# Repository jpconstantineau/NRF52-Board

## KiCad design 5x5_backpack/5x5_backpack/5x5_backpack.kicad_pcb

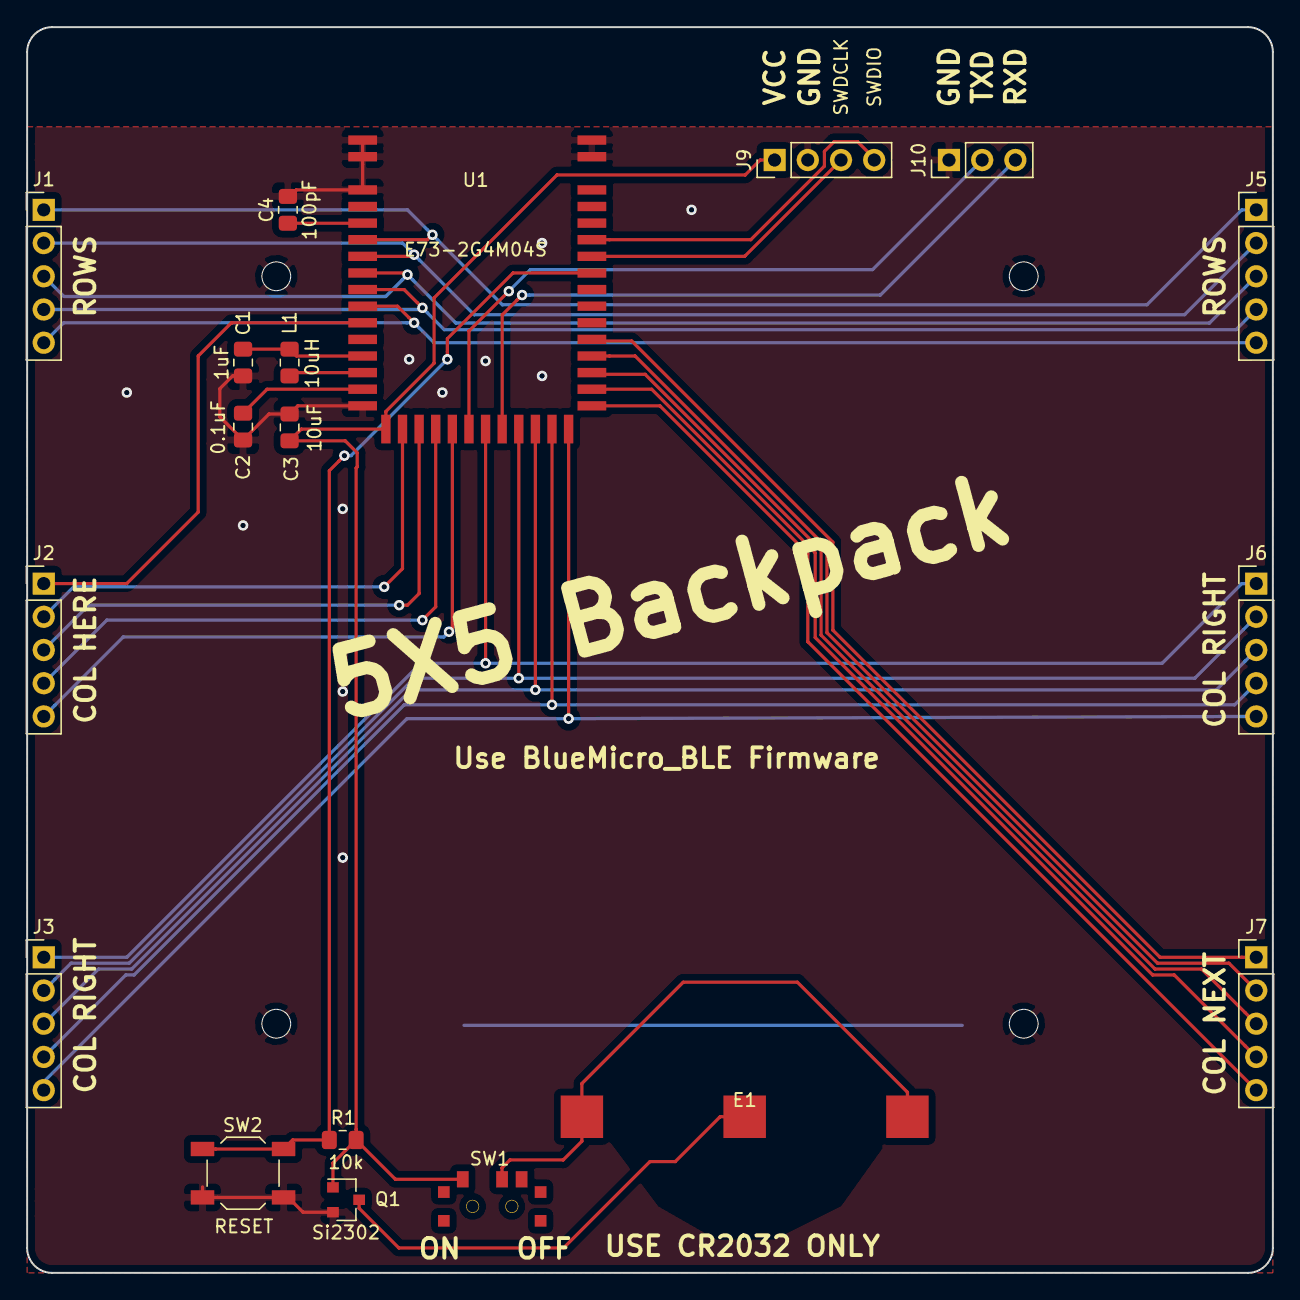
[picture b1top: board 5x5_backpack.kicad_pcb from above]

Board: 2 copper layers, 95.2 x 95.2 mm, 23 parts (0 on the bottom side), 33 nets.

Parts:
C1: 1uF; C_0805_2012Metric_Pad1.15x1.40mm_HandSolder
C2: 0.1uF; C_0805_2012Metric_Pad1.15x1.40mm_HandSolder
C3: 10uF; C_0805_2012Metric_Pad1.15x1.40mm_HandSolder
C4: 100pF; C_0805_2012Metric_Pad1.15x1.40mm_HandSolder
E1: Battery; C70373_CR2032
J1, J2, J3, J5, J6, J7: Conn_01x04; PinHeader_1x05_P2.54mm_Vertical
J9: Conn_01x04; PinHeader_1x04_P2.54mm_Vertical
J10: Conn_01x03; PinHeader_1x03_P2.54mm_Vertical
J11, J12, J13, J14: Conn_01x01; MountingHole_2.2mm_M2_ISO7380
L1: 10uH; C_0805_2012Metric_Pad1.15x1.40mm_HandSolder
Q1: Si2302; SOT-23
R1: 10k; C_0805_2012Metric_Pad1.15x1.40mm_HandSolder
SW1: SW_SPDT; SPDT_C128955
SW2: RESET; SW_TACT_ALPS_SKQGABE010
U1: E73-2G4M04S

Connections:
COL1: J2.1, U1.10
COL2: J2.2, U1.17
COL3: J2.3, U1.18
COL4: J2.4, U1.19
COL5: J2.5, U1.20
COL6: J3.1, J6.1, U1.22
COL7: J3.2, J6.2, U1.24
COL8: J3.3, J6.3, U1.25
COL9: J3.4, J6.4, U1.26
COL10: J3.5, J6.5, U1.27
COL11: J7.1, U1.32
COL12: J7.2, U1.31
COL13: J7.3, U1.30
COL14: J7.4, U1.29
COL15: J7.5, U1.28
GND: C1.2, C2.2, C3.2, C4.2, J9.2, J10.1, J11.1, J12.1, J13.1, J14.1, Q1.2, SW2.1, U1.0, U1.1, U1.2, U1.15, U1.42, U1.43
unnamed: C1.1, L1.1, U1.12
unnamed: C2.1, U1.14
unnamed: C4.1, U1.4
unnamed: E1.1, SW1.2
unnamed: E1.2, Q1.3
unnamed: L1.2, U1.13
RESET: R1.2, SW2.2, U1.36
ROW1: J1.1, J5.1, U1.5
ROW2: J1.2, J5.2, U1.6
ROW3: J1.3, J5.3, U1.7
ROW4: J1.4, J5.4, U1.8
ROW5: J1.5, J5.5, U1.9
RXD: J10.3, U1.23
SWDCLK: J9.3, U1.37
SWDIO: J9.4, U1.38
TXD: J10.2, U1.21
VCC: C3.1, J9.1, Q1.1, R1.1, SW1.1, U1.16

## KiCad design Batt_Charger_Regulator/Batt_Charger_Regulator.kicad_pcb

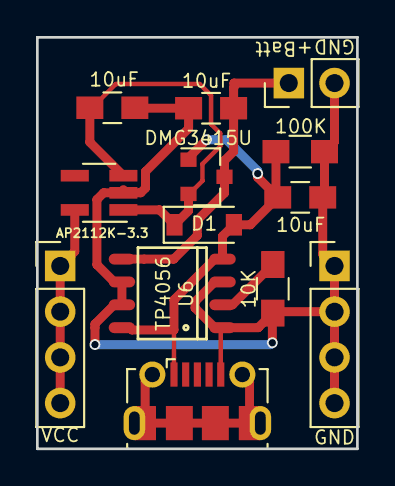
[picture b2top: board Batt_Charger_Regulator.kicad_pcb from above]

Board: 2 copper layers, 17.8 x 22.9 mm, 13 parts (0 on the bottom side), 6 nets.

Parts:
C5, C7, C8: 10uF; C_0805_HandSoldering
D1: MBR120; D_SOD-123
J1: USB_OTG; USB_Micro-B_Molex-105017-0001
J2, J4: Conn_01x04; Pin_Header_Straight_1x04_Pitch2.54mm
J3: Conn_01x02; Pin_Header_Straight_1x02_Pitch2.54mm
Q1: DMG3415U; SOT-23
R2: 100K; R_0805_HandSoldering
R3: 10K; R_0805_HandSoldering
U3: AP2112K-3.3; SOT-23-5_HandSoldering
U6: TP4056; SO-8

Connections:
/VBatt: C7.1, J3.1, Q1.3, U6.5
/VBus: C8.1, D1.2, J1.1, Q1.1, R2.1, U6.4, U6.8
GND: C5.2, C7.2, C8.2, J1.5, J2.1, J2.2, J2.3, J2.4, J3.2, R2.2, R3.2, U3.2, U6.1, U6.3, U6.6, U6.7
unnamed: C5.1, D1.1, Q1.2, U3.1, U3.3
unnamed: R3.1, U6.2
VCC: J4.1, J4.2, J4.3, J4.4, U3.5

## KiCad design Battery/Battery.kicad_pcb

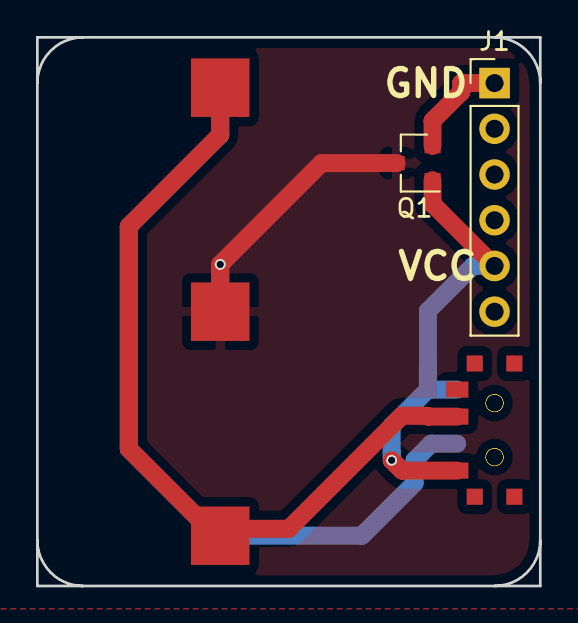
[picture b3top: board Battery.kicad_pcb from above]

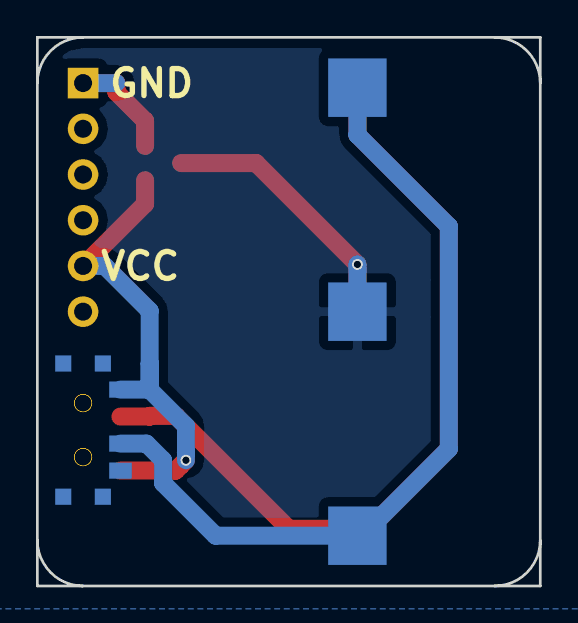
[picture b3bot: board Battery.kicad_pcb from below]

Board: 2 copper layers, 27.9 x 30.5 mm, 6 parts (2 on the bottom side), 5 nets.

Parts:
BT1, BT2: Battery_Cell; C70373_CR2032
J1: Conn_01x06; Pin_Header_Straight_1x06_Pitch2.54mm
Q1: BSS138; SOT-23
SW1, SW2: SW_SPDT; SPDT_C128955

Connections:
GND: BT1.2, BT2.2, Q1.3
unnamed: BT1.1, SW1.2
unnamed: BT2.1, SW2.2
unnamed: J1.1, Q1.2
VCC: J1.5, Q1.1, SW1.1, SW2.1

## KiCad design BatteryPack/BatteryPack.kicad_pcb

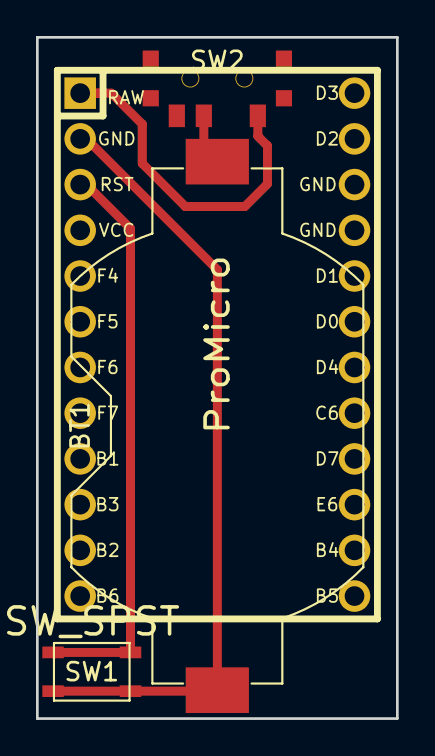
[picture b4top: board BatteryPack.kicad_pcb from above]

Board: 2 copper layers, 20.0 x 37.8 mm, 4 parts (0 on the bottom side), 4 nets.

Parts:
BT1: Battery_Cell; Keystone_1058_1x2032-CoinCell
SW1: SW_SPST; SW_TACT_TS-1145A_C318904
SW2: SW_SPDT; SPDT_C128955
U1: ProMicro; Pro_Micro

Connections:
GND: BT1.2, SW1.2, U1.2
unnamed: BT1.1, SW2.2
unnamed: SW1.1, U1.3
unnamed: SW2.1, U1.1

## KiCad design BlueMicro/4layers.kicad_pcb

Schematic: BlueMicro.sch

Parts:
C1: 1uF; C_0603_1608Metric
C2, C10: 0.1uF; C_0603_1608Metric
C3, C11, C12, C13: 10uF; C_0603_1608Metric
C4: 100pF; C_0603_1608Metric
C5, C8: 22pF; C_0603_1608Metric
C6, C7, C9: 100nF; C_0603_1608Metric
C14: 1nF; C_0603_1608Metric
D1: BLUE; LED_0603_1608Metric
D2, D5, D6, D10: RED; LED_0603_1608Metric
D3, D4, D7: 1N4148W; D_SOD-123
D8: B5819W; D_SOD-123
D9: GREEN; LED_0603_1608Metric
J9: Conn_01x04; PinHeader_1x04_P2.54mm_Vertical
J10: Conn_01x02; PinHeader_1x02_P2.54mm_Vertical
J17: USB_B_Micro; USB_Micro-B_Molex-105017-0001
L1: 10uH; L_0603_1608Metric
Q1: Si2301CDS; SOT-23
R1, R7, R9: 10k; R_0603_1608Metric
R2, R3, R4, R5, R6, R10: 1k; R_0603_1608Metric
R8: 100k; R_0603_1608Metric
R11: 806k; R_0603_1608Metric
R12: 2M; R_0603_1608Metric
TP1, TP2, TP3, TP4, TP5, TP6, TP7: TestPoint_Probe; TestPoint_Pad_1.0x1.0mm
U1: E73-2G4M04S
U2: CH340G; SOP-16_4.4x10.4mm_P1.27mm
U3: TP4056; SSOP-8_3.95x5.21x3.27mm_P1.27mm
U4: AP2112K-3.3; SOT-23-5
U5: ProMicro; Pro_Micro
Y1: 12MHz; Crystal_SMD_3225-4Pin_3.2x2.5mm

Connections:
B1: U1.27, U5.9
B2: U1.28, U5.11
B3: U1.29, U5.10
B4: U1.30, U5.23
B5: U1.31, U5.24
B6: U1.26, U5.12
BLUELED: D1.2, U1.34
C6: U1.8, U5.20
D0: U1.6, U5.18
D1: U1.5, U5.17
D2: U1.22, U5.14
D3: U1.33, U5.13
D4: U1.7, U5.19
D7: U1.9, U5.21
DFU: TP4.1, U1.35
DTR: C10.2, U2.13
E6: U1.10, U5.22
F4: U1.20, U5.5
F5: U1.19, U5.6
F6: U1.18, U5.7
F7: U1.17, U5.8
FACTORYRESET: TP3.1, U1.39
GND: C1.2, C2.2, C3.2, C4.2, C5.2, C6.2, C7.2, C8.2, C9.2, C11.2, C12.2, C13.2, C14.2, J9.2, J10.2, J17.5, R2.2, R3.2, R7.1, R8.1, R12.2, U1.0, U1.1, U1.2, U1.15, U1.42, U1.43, U2.1, U3.1, U3.3, U4.2, U5.2, U5.15, U5.16, Y1.2, Y1.4; also elsewhere on the board
NFC1: TP5.1, U1.24
NFC2: TP6.1, U1.25
unnamed: C1.1, L1.1, U1.12
unnamed: C2.1, U1.14
unnamed: C4.1, U1.4
unnamed: C5.1, U2.7, Y1.1
unnamed: C7.1, U2.4
unnamed: C8.1, U2.8, Y1.3
unnamed: C9.1, D4.1, R5.2, R6.1, U2.16
unnamed: C12.1, D8.1, Q1.2 (S), U4.1, U4.3
unnamed: C14.1, R11.2, R12.1, U1.11
unnamed: D1.1, R2.1
unnamed: D2.1, R3.1
unnamed: D3.1, D4.2
unnamed: D5.2, R5.1
unnamed: D6.2, R6.2
unnamed: D9.1, U3.6
unnamed: D9.2, R9.2
unnamed: D10.1, U3.7
unnamed: D10.2, R10.2
unnamed: J17.2, U2.6
unnamed: J17.3, U2.5
unnamed: L1.2, U1.13
unnamed: R4.1, U2.2
unnamed: R7.2, U3.2
PWM: TP2.1, U1.40
REDLED: D2.2, U1.32
RESET: C10.1, D7.2, R1.2, U1.36, U5.3; also elsewhere on the board
RXD: D6.1, R4.2, U1.23
SWDCLK: J9.3, U1.37
SWDIO: J9.4, U1.38
TXD: D5.1, U1.21, U2.3
VBATT: C13.1, J10.1, Q1.3 (D), R11.1, U3.5
VBUS: C6.1, C11.1, D3.2, D8.2, J17.1, Q1.1 (G), R8.2, R9.1, R10.1, U3.4, U3.8
VCC: C3.1, D7.1, J9.1, R1.1, U1.16, U4.5, U5.4
WS2812B: TP1.1, U1.41

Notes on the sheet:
1 - diodes provide close enough to 3.3v for the serial chip. 2 - To ensure low battery consumption when USB is not connected, Only GND is shared.

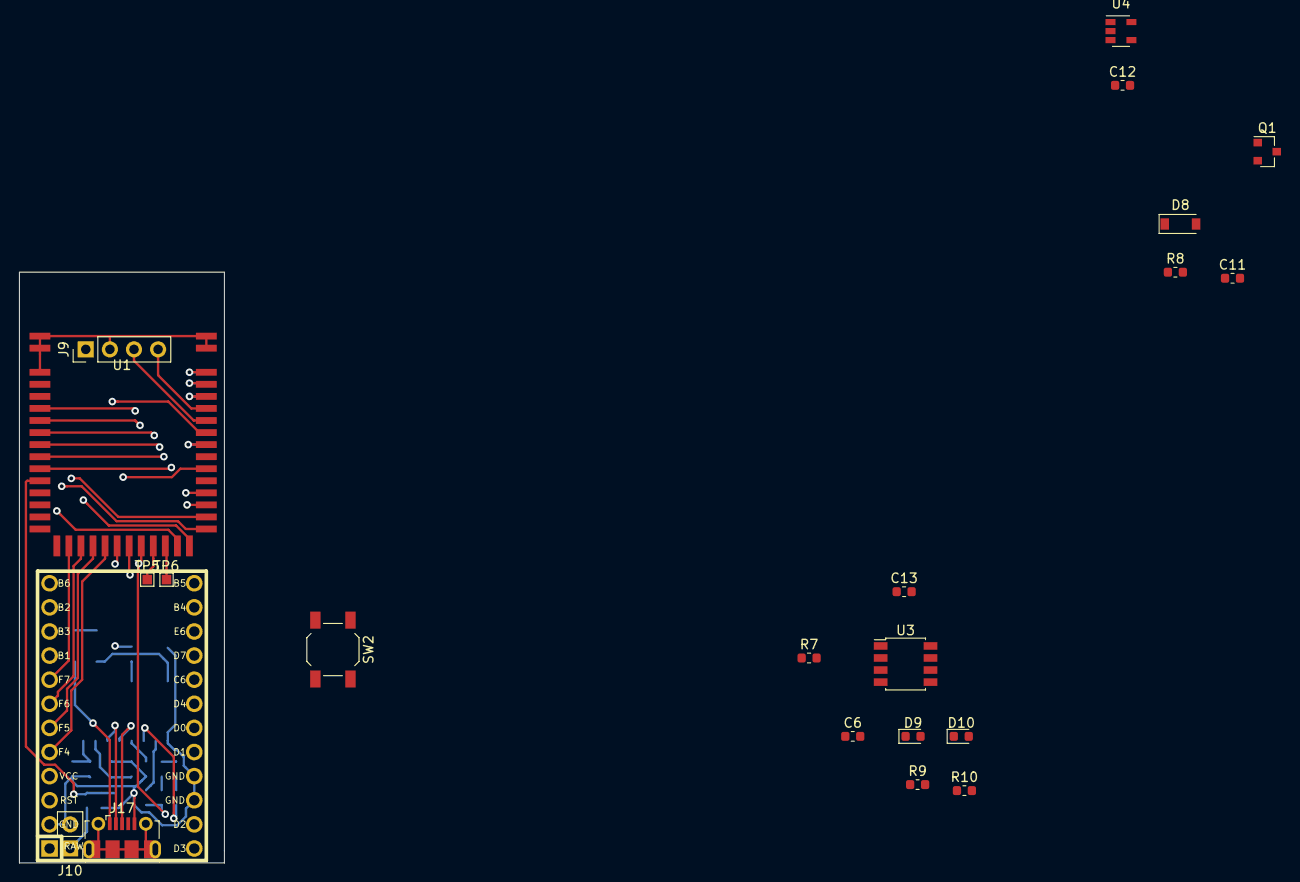
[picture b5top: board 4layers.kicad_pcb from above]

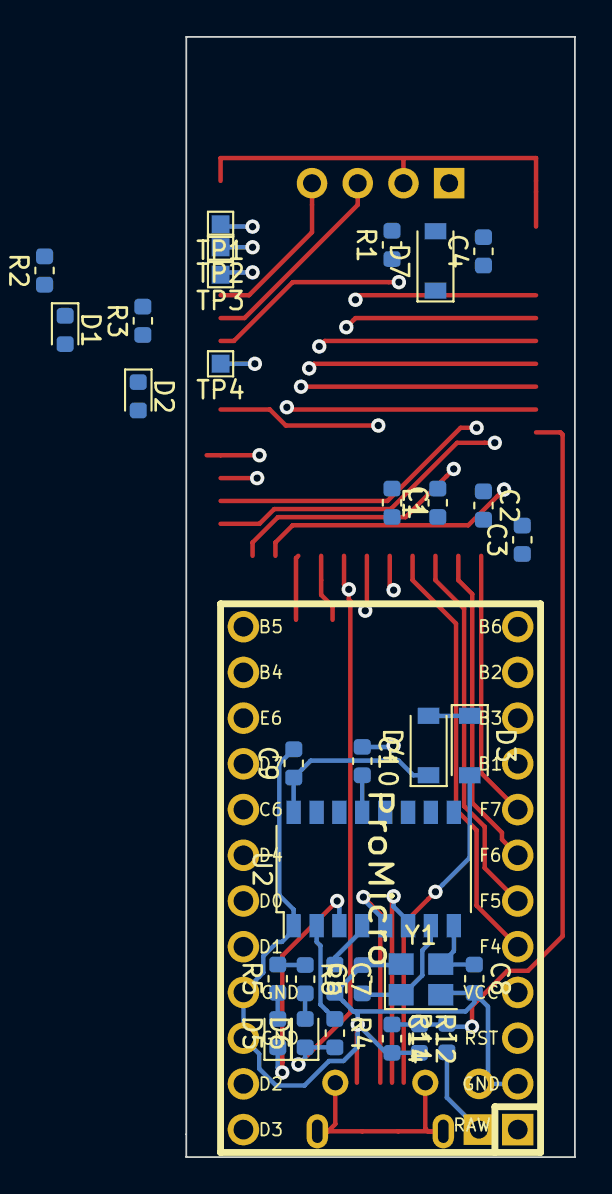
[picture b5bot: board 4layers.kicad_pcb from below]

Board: 4 copper layers, 21.6 x 62.2 mm, 54 parts (33 on the bottom side), 59 nets.

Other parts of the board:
SW2: RESET; SW_TACT_ALPS_SKQGABE010

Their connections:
GND: SW2.1; also elsewhere on the board
RESET: SW2.2; also elsewhere on the board

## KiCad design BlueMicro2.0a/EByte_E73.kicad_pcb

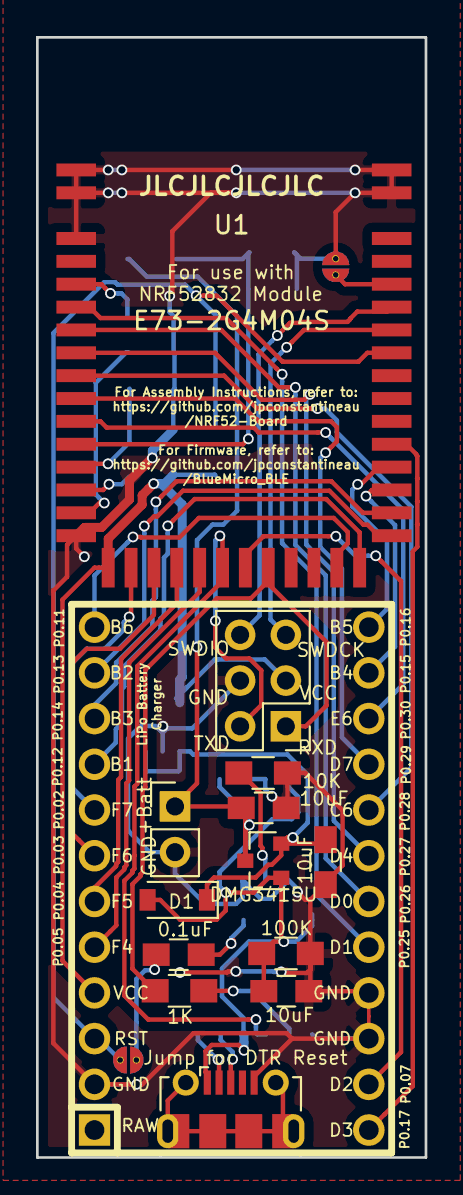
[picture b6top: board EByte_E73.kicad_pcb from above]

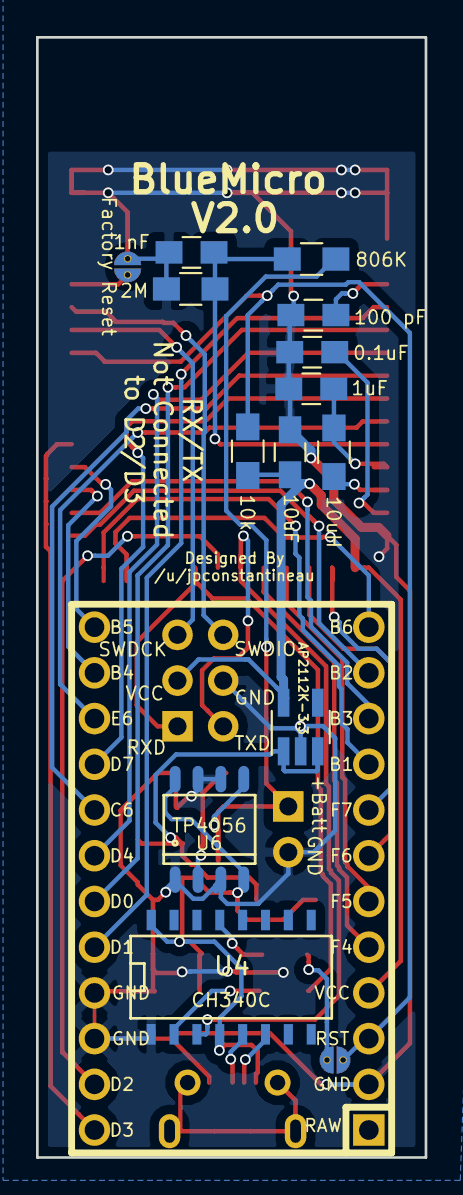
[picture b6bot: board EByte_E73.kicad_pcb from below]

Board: 2 copper layers, 21.6 x 62.2 mm, 28 parts (13 on the bottom side), 40 nets.

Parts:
C1: 1uF; C_0805_HandSoldering
C2, C9: 0.1uF; C_0805_HandSoldering
C3, C5, C7, C8: 10uF; C_0805_HandSoldering
C4: 100 pF; C_0805_HandSoldering
C6: 1nF; C_0805_HandSoldering
D1: MBR120; D_SOD-123
J1: USB_OTG; USB_Micro-B_Molex-105017-0001
J2: Serial Connector; Pin_Header_Straight_2x03_Pitch2.54mm
J3: Conn_01x02; Pin_Header_Straight_1x02_Pitch2.54mm
JP1: JUMPER-SMT_2_NO; SolderJumperSingle
JP2: Factory Reset; SolderJumperSingle
L1: 10uH; L_0805_HandSoldering
Q1: DMG3415U; SOT-23
R1: 10k; R_0805_HandSoldering
R2: 100K; R_0805_HandSoldering
R3: 10K; R_0805_HandSoldering
R4: 806K; R_0805_HandSoldering
R5: 2M; R_0805_HandSoldering
R6: 1K; R_0805_HandSoldering
U1: E73-2G4M04S
U2: ProMicro; Pro_Micro
U3: AP2112K-3.3; SOT-23-5_HandSoldering
U4: CH340C; SO-16-N
U6: TP4056; SO-8

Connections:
/DTR: C9.2, U4.13
/Data+: J1.3, U4.5
/Data-: J1.2, U4.6
/P0.02: U1.17, U2.8
/P0.03: U1.18, U2.7
/P0.04: U1.19, U2.6
/P0.05: U1.20, U2.5
/P0.07: U1.22, U2.14
/P0.11: U1.26, U2.12
/P0.15: U1.30, U2.23
/P0.16: U1.31, U2.24
/P0.17: U1.32, U2.13
/P0.27: U1.7, U2.19
/P0.28: U1.8, U2.20
/P0.29: U1.9, U2.21
/P0.30: U1.10, U2.22
/P0.31: C6.1, R4.2, R5.1, U1.11
/VBatt: C7.1, J3.1, Q1.3, R4.1, U6.5
/VBus: C8.1, D1.2, J1.1, Q1.1, R2.1, U4.4, U4.16, U6.4, U6.8
GND: C1.2, C2.2, C3.2, C4.2, C5.2, C6.2, C7.2, C8.2, J1.5, J2.4, J3.2, JP2.2, R2.2, R3.2, R5.2, U1.0, U1.1, U1.2, U1.15, U1.42, U1.43, U2.2, U2.15, U2.16, U3.2, U4.1, U6.1, U6.3, U6.6, U6.7
MISO: U1.29, U2.10
MOSI: U1.28, U2.11
unnamed: C1.1, L1.1, U1.12
unnamed: C2.1, U1.14
unnamed: C4.1, U1.4
unnamed: C5.1, D1.1, Q1.2, U3.1, U3.3
unnamed: C9.1, JP1.2
unnamed: JP2.1, U1.39
unnamed: L1.2, U1.13
unnamed: R3.1, U6.2
unnamed: R6.2, U4.2
RESET: JP1.1, R1.1, U1.36, U2.3
RXD: J2.1, R6.1, U1.23
SCK: U1.27, U2.9
SCL: U1.6, U2.18
SDA: U1.5, U2.17
SWDCLK: J2.5, U1.37
SWDIO: J2.6, U1.38
TXD: J2.2, U1.21, U4.3
VCC: C3.1, J2.3, R1.2, U1.16, U2.4, U3.5
